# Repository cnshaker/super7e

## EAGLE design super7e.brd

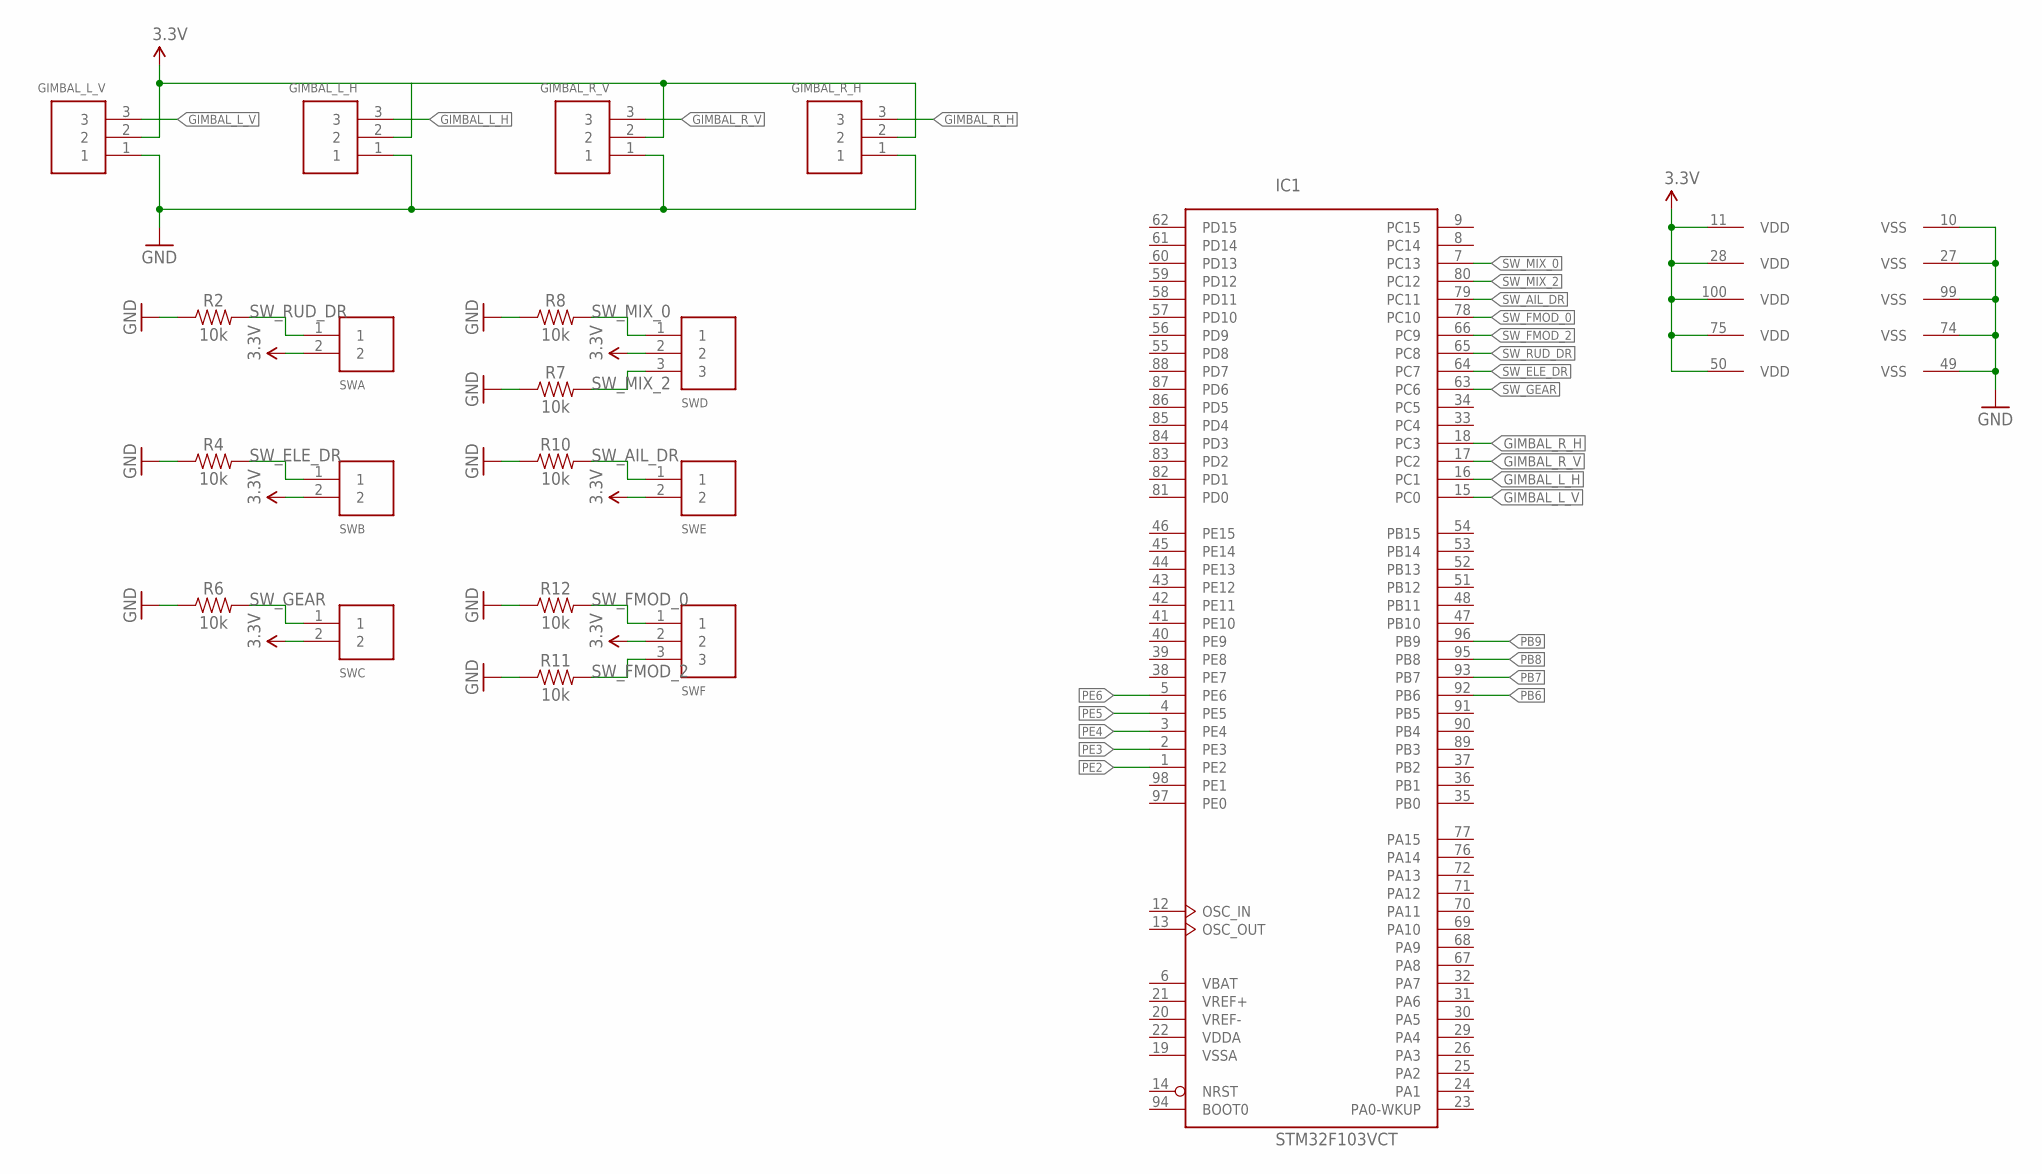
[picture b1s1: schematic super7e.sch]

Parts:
GIMBAL_L_H: 3PIN; B3B-PH-K-S
GIMBAL_L_V: 3PIN; B3B-PH-K-S
GIMBAL_R_H: 3PIN; B3B-PH-K-S
GIMBAL_R_V: 3PIN; B3B-PH-K-S
IC1: STM32F103VCT; LQFP100
R2, R4, R6, R7, R8, R10, R11, R12: 10k; 0603
SWA: 2PIN; B2B-PH-K-S
SWB: 2PIN; B2B-PH-K-S
SWC: 2PIN; B2B-PH-K-S
SWD: 3PIN; B3B-PH-K-S
SWE: 2PIN; B2B-PH-K-S
SWF: 3PIN; B3B-PH-K-S

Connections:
3.3V: GIMBAL_L_H.2, GIMBAL_L_V.2, GIMBAL_R_H.2, GIMBAL_R_V.2, IC1.11 (VDD), IC1.28 (VDD), IC1.50 (VDD), IC1.75 (VDD), IC1.100 (VDD), SWA.2, SWB.2, SWC.2, SWD.2, SWE.2, SWF.2
GIMBAL_L_H: GIMBAL_L_H.3, IC1.16 (PC1)
GIMBAL_L_V: GIMBAL_L_V.3, IC1.15 (PC0)
GIMBAL_R_H: GIMBAL_R_H.3, IC1.18 (PC3)
GIMBAL_R_V: GIMBAL_R_V.3, IC1.17 (PC2)
GND: GIMBAL_L_H.1, GIMBAL_L_V.1, GIMBAL_R_H.1, GIMBAL_R_V.1, IC1.10 (VSS), IC1.27 (VSS), IC1.49 (VSS), IC1.74 (VSS), IC1.99 (VSS), R2.1, R4.1, R6.1, R7.1, R8.1, R10.1, R11.1, R12.1
PB6: IC1.92 (PB6)
PB7: IC1.93 (PB7)
PB8: IC1.95 (PB8)
PB9: IC1.96 (PB9)
PE2: IC1.1 (PE2)
PE3: IC1.2 (PE3)
PE4: IC1.3 (PE4)
PE5: IC1.4 (PE5)
PE6: IC1.5 (PE6)
SW_AIL_DR: IC1.79 (PC11), R10.2, SWE.1
SW_ELE_DR: IC1.64 (PC7), R4.2, SWB.1
SW_FMOD_0: IC1.78 (PC10), R12.2, SWF.1
SW_FMOD_2: IC1.66 (PC9), R11.2, SWF.3
SW_GEAR: IC1.63 (PC6), R6.2, SWC.1
SW_MIX_0: IC1.7 (PC13), R8.2, SWD.1
SW_MIX_2: IC1.80 (PC12), R7.2, SWD.3
SW_RUD_DR: IC1.65 (PC8), R2.2, SWA.1
VBAT: IC1.6 (VBAT)
VDDA: IC1.22 (VDDA)
VREF+: IC1.21 (VREF+)
VREF-: IC1.20 (VREF-)
VSSA: IC1.19 (VSSA)

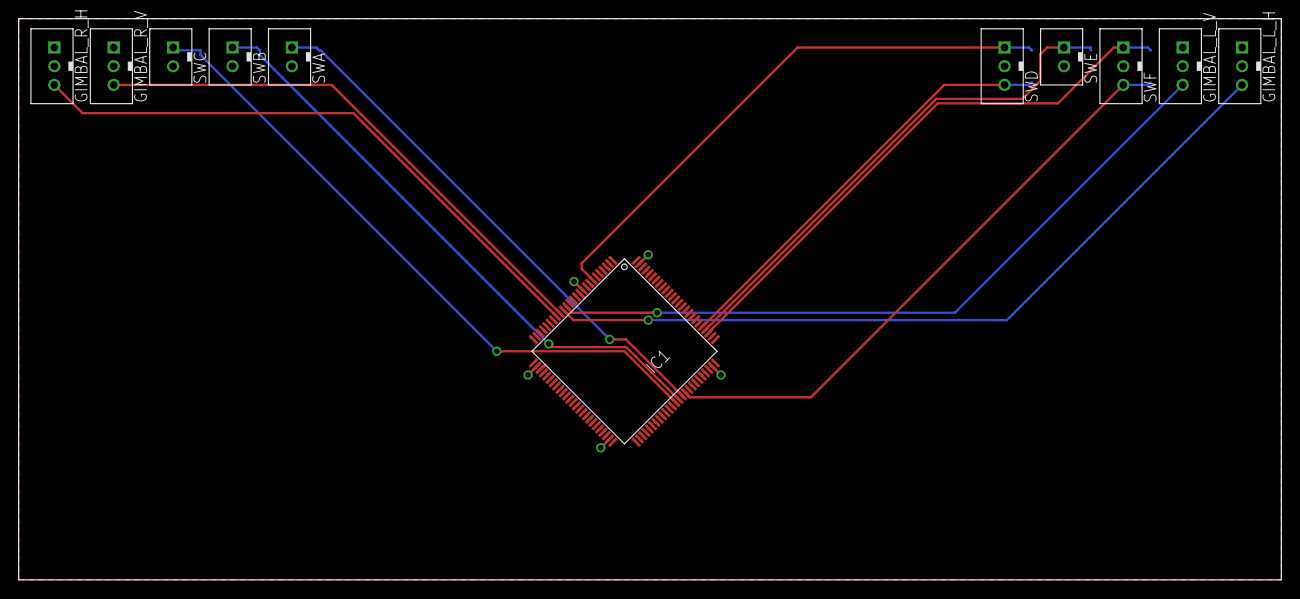
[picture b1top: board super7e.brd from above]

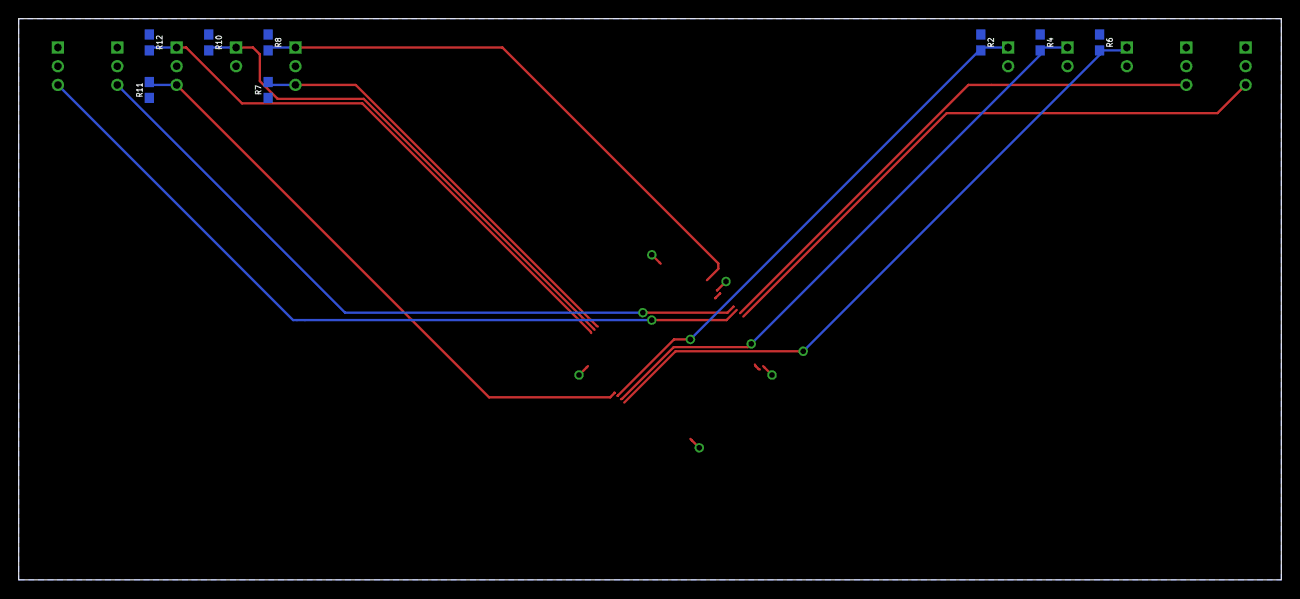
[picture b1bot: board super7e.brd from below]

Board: 2 copper layers, 135.0 x 60.0 mm, 19 parts (8 on the bottom side), 14 nets.

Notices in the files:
parts and their libraries:
SparkFun-Resistors: Licensing: Creative Commons ShareAlike 4.0 International - https://creativecommons.org/licenses/by-sa/4.0
